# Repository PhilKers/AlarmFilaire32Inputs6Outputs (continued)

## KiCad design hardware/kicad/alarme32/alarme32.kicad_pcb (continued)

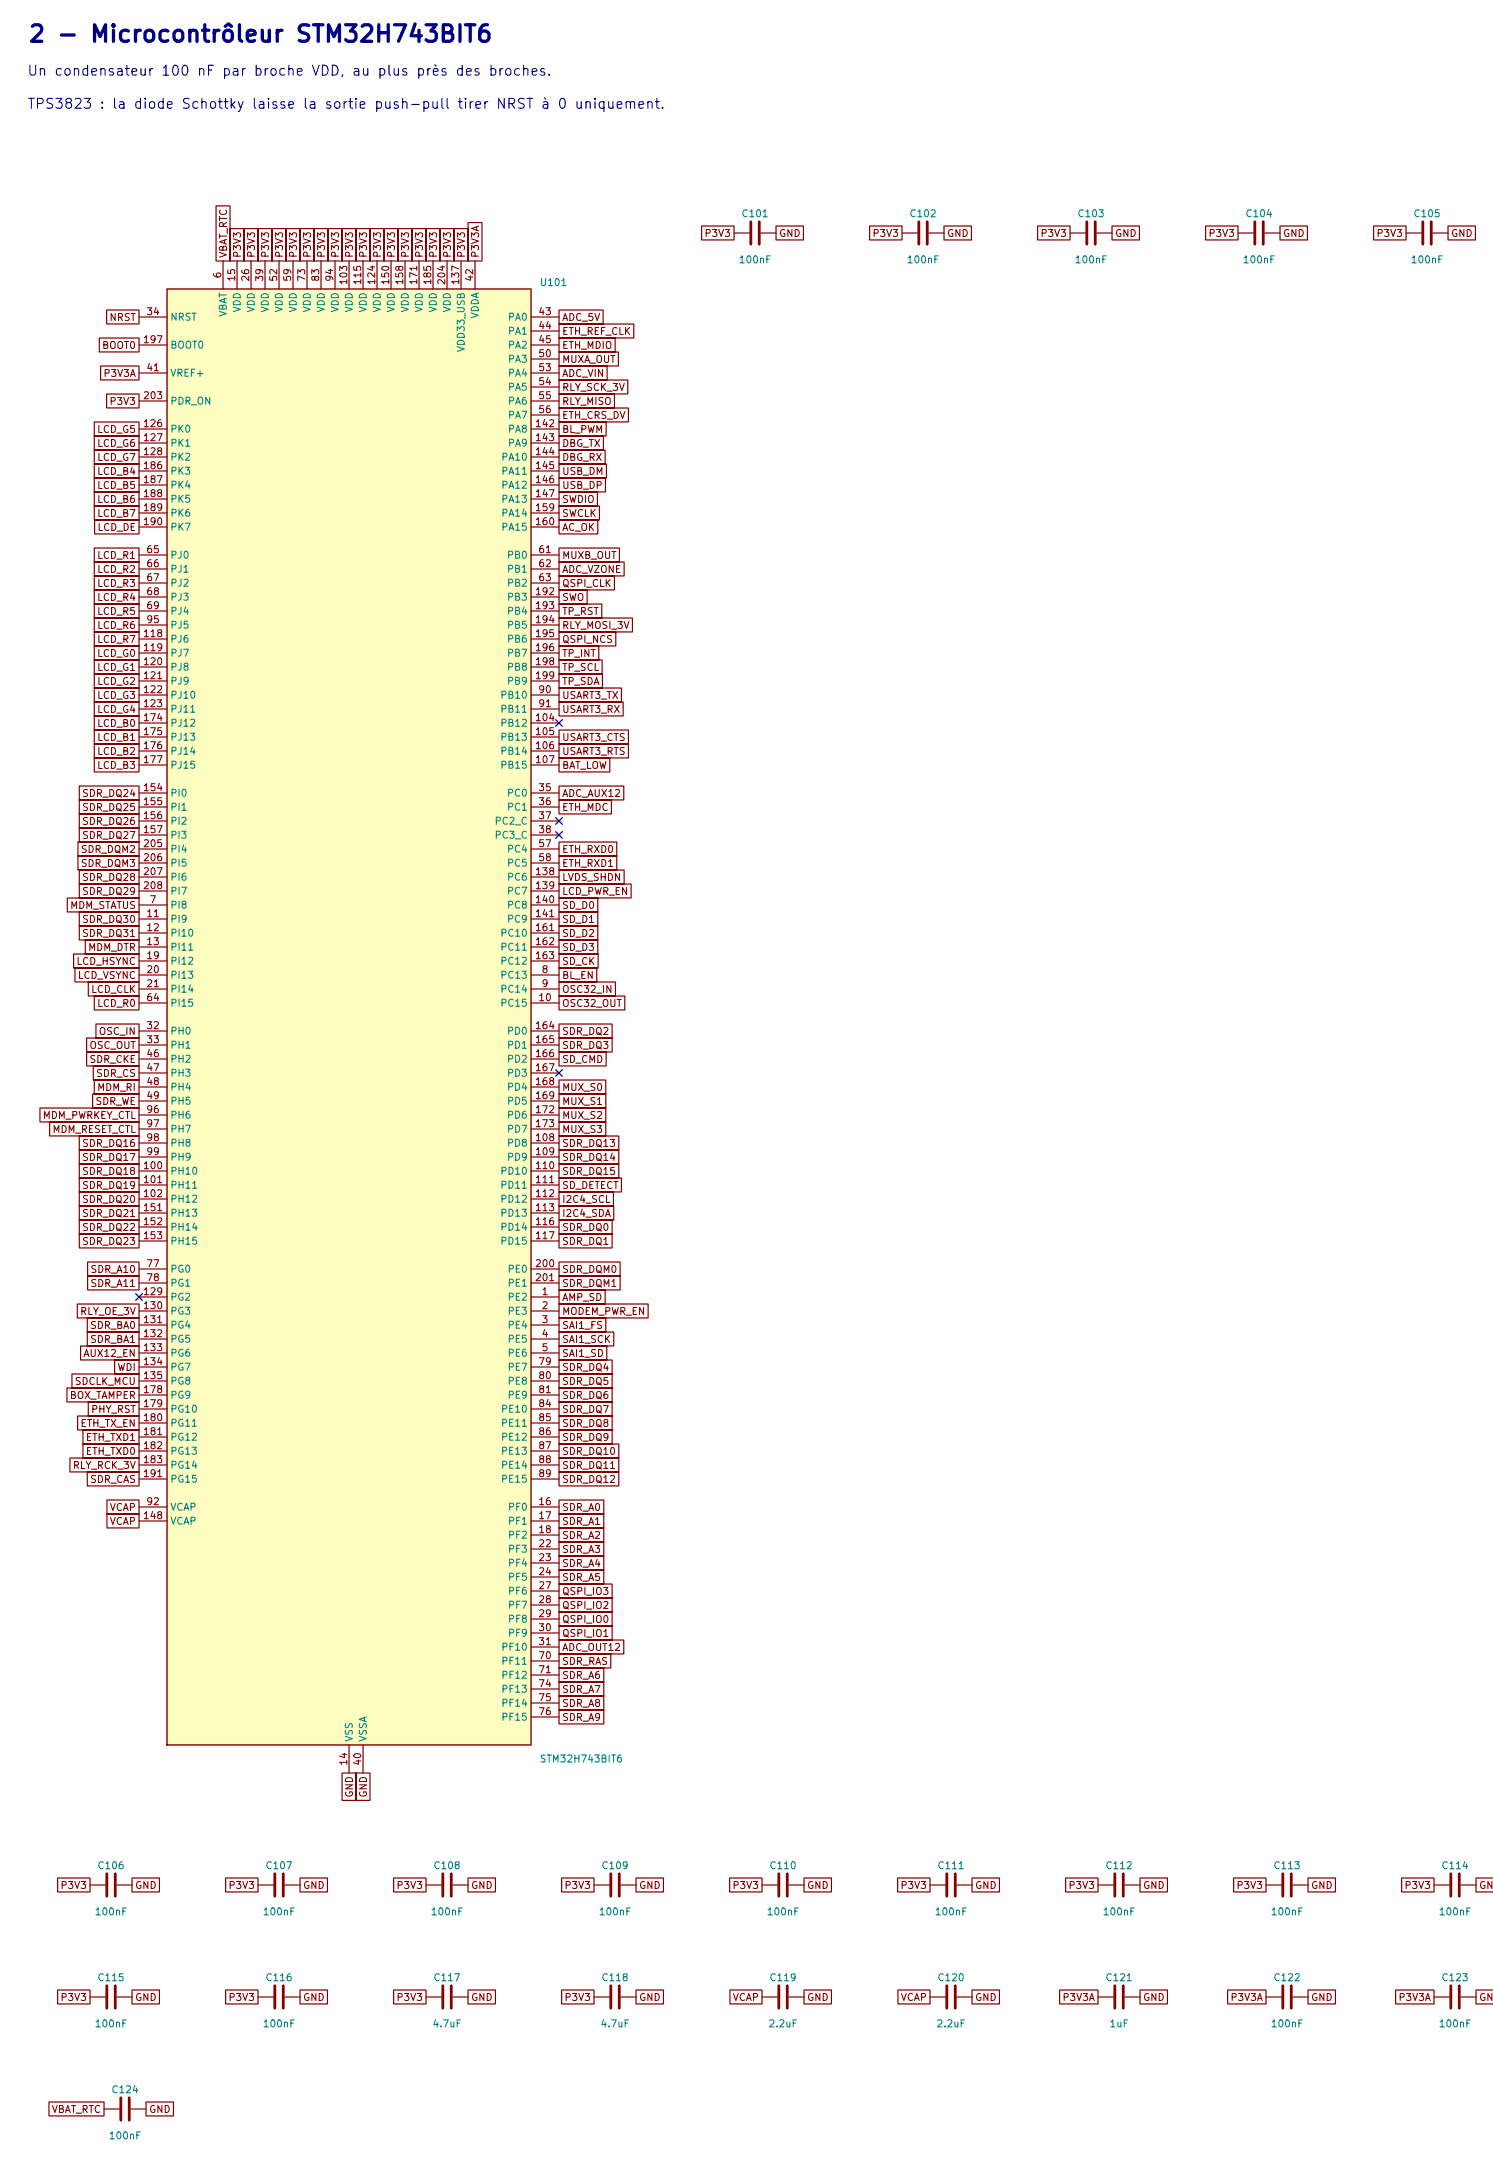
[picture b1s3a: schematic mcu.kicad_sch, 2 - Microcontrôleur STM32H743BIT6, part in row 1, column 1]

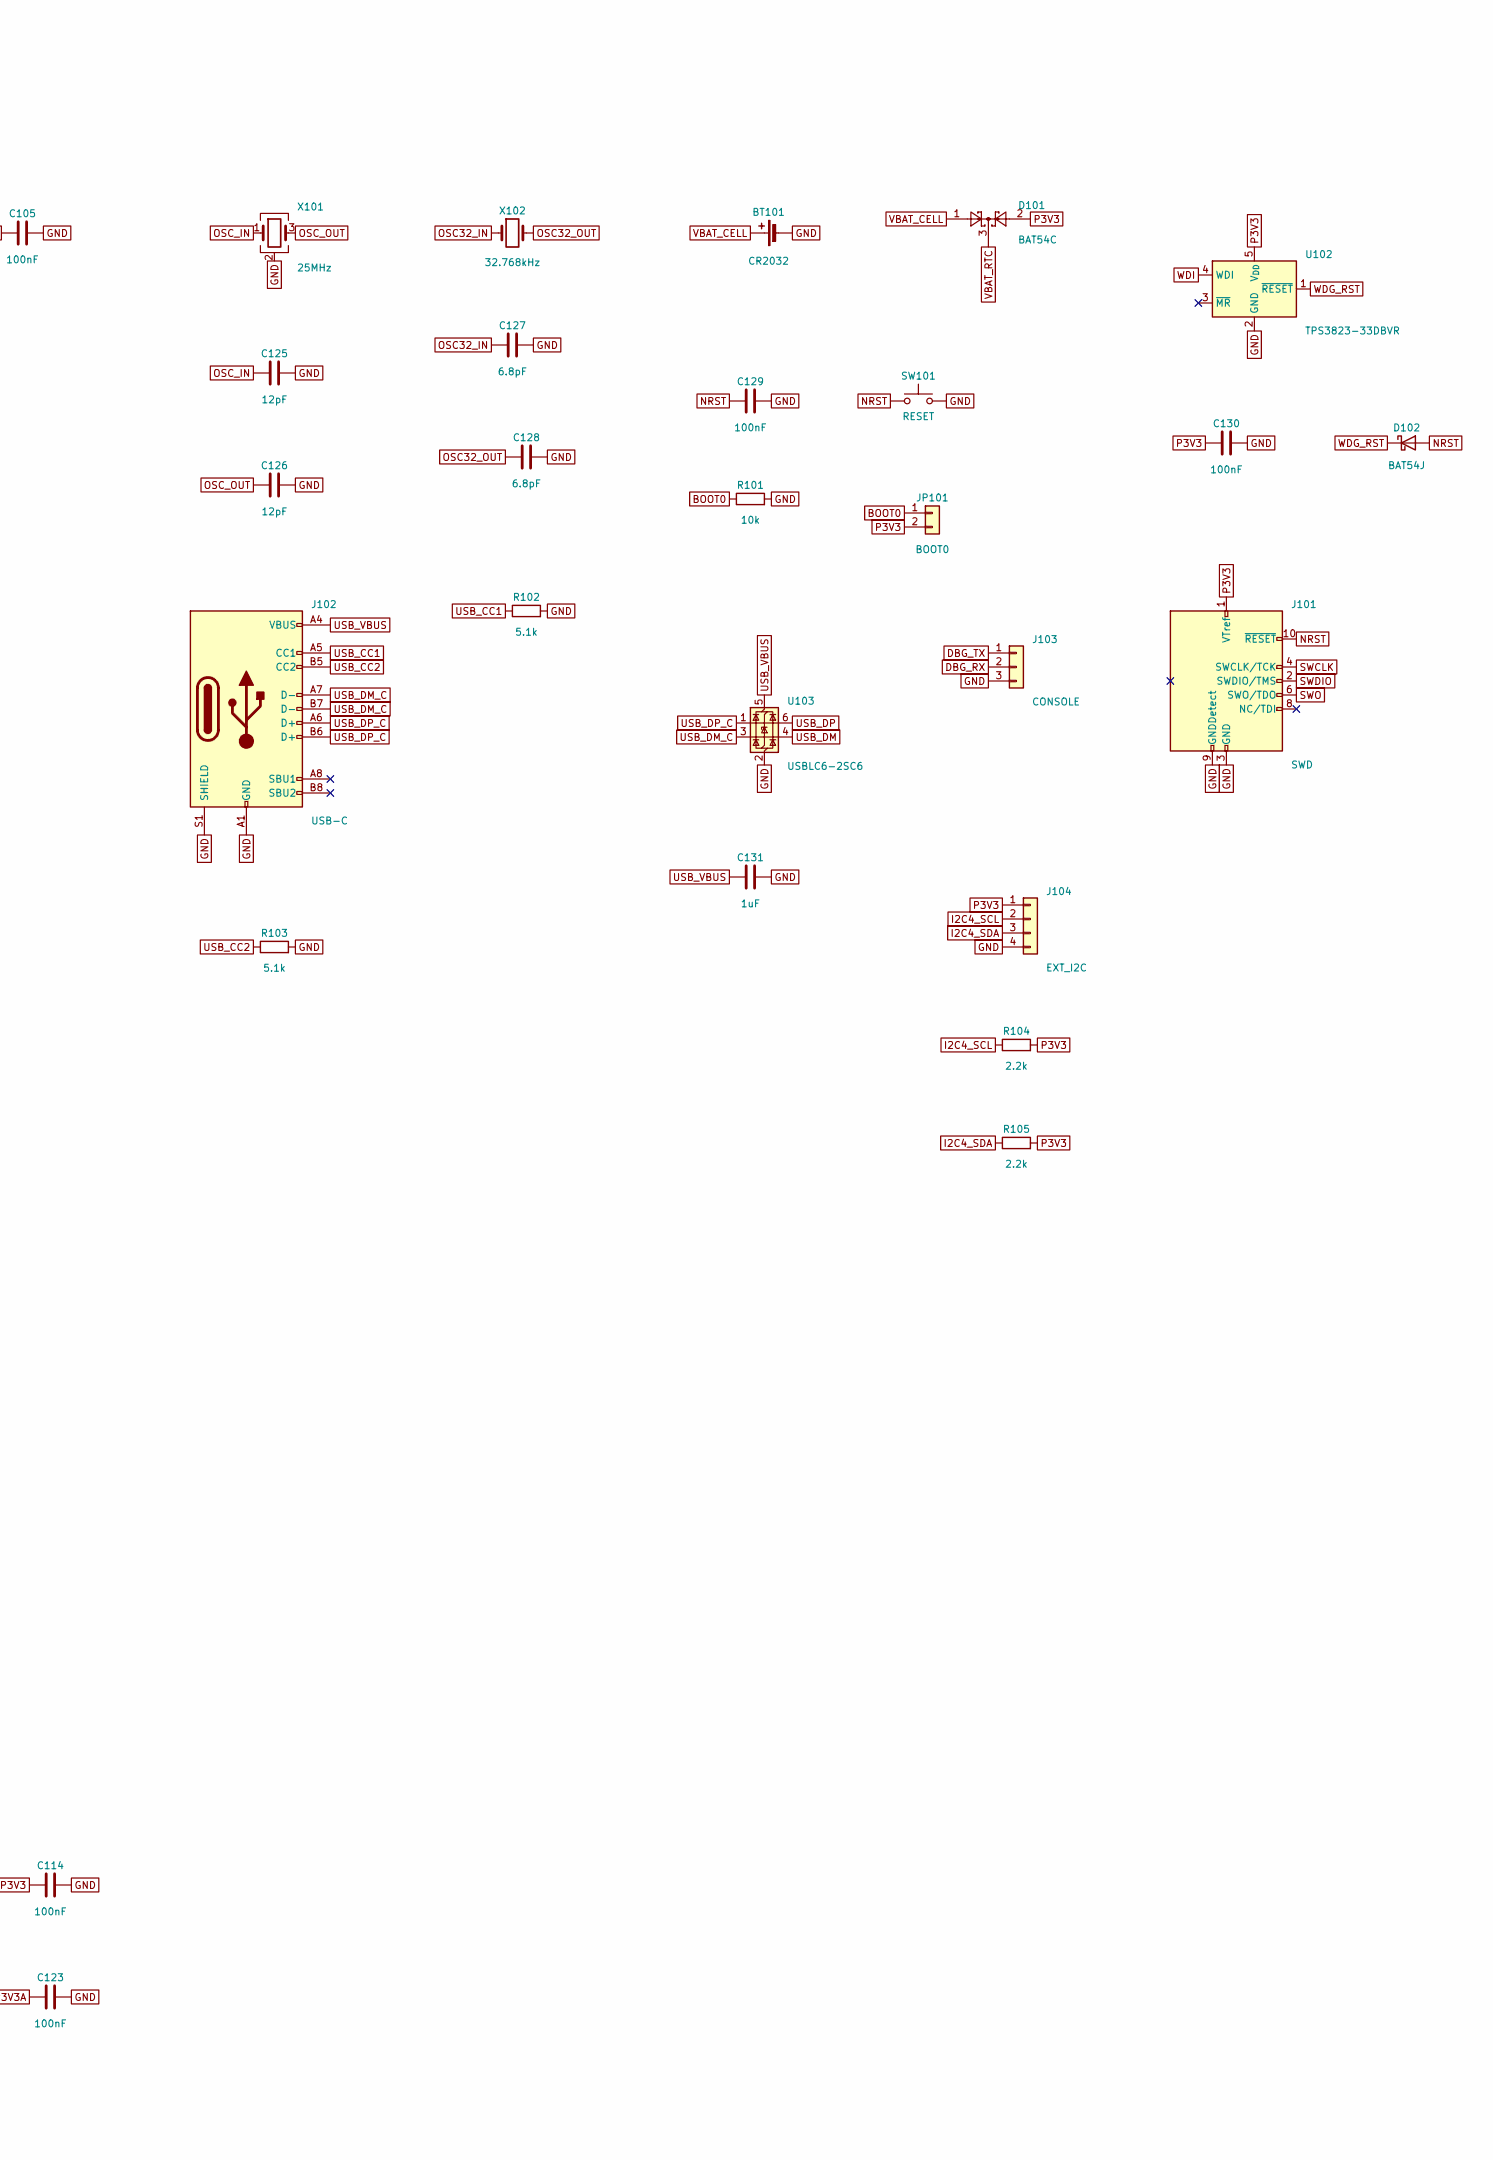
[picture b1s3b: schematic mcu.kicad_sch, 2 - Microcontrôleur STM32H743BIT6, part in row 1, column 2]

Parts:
BT101: CR2032; BatteryHolder_Keystone_3034_1x20mm
C101, C102, C103, C104, C105, C106, C107, C108, C109, C110, C111, C112, C113, C114, C115, C116, C122, C123, C124, C129, C130: 100nF; C_0603_1608Metric
C117, C118: 4.7uF; C_0805_2012Metric
C119, C120: 2.2uF; C_0603_1608Metric
C121, C131: 1uF; C_0603_1608Metric
C125, C126: 12pF; C_0603_1608Metric
C127, C128: 6.8pF; C_0603_1608Metric
D101: BAT54C; SOT-23
D102: BAT54J; D_SOD-323
J101: SWD; PinHeader_2x05_P1.27mm_Vertical
J102: USB-C; USB_C_Receptacle_HRO_TYPE-C-31-M-12
J103: CONSOLE; PinHeader_1x03_P2.54mm_Vertical
J104: EXT_I2C; PinHeader_1x04_P2.54mm_Vertical
JP101: BOOT0; PinHeader_1x02_P2.54mm_Vertical
R101: 10k; R_0603_1608Metric
R102, R103: 5.1k; R_0603_1608Metric
R104, R105: 2.2k; R_0603_1608Metric
SW101: RESET; SW_SPST_EVQP2
U101: STM32H743BIT6; LQFP-208_28x28mm_P0.5mm
U102: TPS3823-33DBVR; SOT-23-5
U103: USBLC6-2SC6; SOT-23-6
X101: 25MHz; Crystal_SMD_3225-4Pin_3.2x2.5mm
X102: 32.768kHz; Crystal_SMD_3215-2Pin_3.2x1.5mm

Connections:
AC_OK: U101.160 (PA15); also elsewhere on the board
ADC_5V: U101.43 (PA0); also elsewhere on the board
ADC_AUX12: U101.35 (PC0); also elsewhere on the board
ADC_OUT12: U101.31 (PF10); also elsewhere on the board
ADC_VIN: U101.53 (PA4); also elsewhere on the board
ADC_VZONE: U101.62 (PB1); also elsewhere on the board
AMP_SD: U101.1 (PE2); also elsewhere on the board
AUX12_EN: U101.133 (PG6); also elsewhere on the board
BAT_LOW: U101.107 (PB15); also elsewhere on the board
BL_EN: U101.8 (PC13); also elsewhere on the board
BL_PWM: U101.142 (PA8); also elsewhere on the board
BOOT0: JP101.1, R101.1, U101.197 (BOOT0)
BOX_TAMPER: U101.178 (PG9); also elsewhere on the board
DBG_RX: J103.2, U101.144 (PA10)
DBG_TX: J103.1, U101.143 (PA9)
ETH_CRS_DV: U101.56 (PA7); also elsewhere on the board
ETH_MDC: U101.36 (PC1); also elsewhere on the board
ETH_MDIO: U101.45 (PA2); also elsewhere on the board
ETH_REF_CLK: U101.44 (PA1); also elsewhere on the board
ETH_RXD0: U101.57 (PC4); also elsewhere on the board
ETH_RXD1: U101.58 (PC5); also elsewhere on the board
ETH_TXD0: U101.182 (PG13); also elsewhere on the board
ETH_TXD1: U101.181 (PG12); also elsewhere on the board
ETH_TX_EN: U101.180 (PG11); also elsewhere on the board
GND: BT101.2 (-), C101.2, C102.2, C103.2, C104.2, C105.2, C106.2, C107.2, C108.2, C109.2, C110.2, C111.2, C112.2, C113.2, C114.2, C115.2, C116.2, C117.2, C118.2, C119.2, C120.2, C121.2, C122.2, C123.2, C124.2, C125.2, C126.2, C127.2, C128.2, C129.2, C130.2, C131.2, J101.3 (GND), J101.5 (GND), J101.9 (GNDDetect), J102.A1 (GND), J102.A12 (GND), J102.B1 (GND), J102.B12 (GND), J102.S1 (SHIELD), J103.3, J104.4, R101.2, R102.2, R103.2, SW101.2, U101.14 (VSS), U101.25 (VSS), U101.40 (VSSA), U101.51 (VSS), U101.60 (VSS), U101.72 (VSS), U101.82 (VSS), U101.93 (VSS), U101.114 (VSS), U101.125 (VSS), U101.136 (VSS), U101.149 (VSS), U101.170 (VSS), U101.184 (VSS), U101.202 (VSS), U102.2 (GND), U103.2 (GND), X101.2 (G), X101.4 (G); also elsewhere on the board
I2C4_SCL: J104.2, R104.1, U101.112 (PD12); also elsewhere on the board
I2C4_SDA: J104.3, R105.1, U101.113 (PD13); also elsewhere on the board
LCD_B0: U101.174 (PJ12); also elsewhere on the board
LCD_B1: U101.175 (PJ13); also elsewhere on the board
LCD_B2: U101.176 (PJ14); also elsewhere on the board
LCD_B3: U101.177 (PJ15); also elsewhere on the board
LCD_B4: U101.186 (PK3); also elsewhere on the board
LCD_B5: U101.187 (PK4); also elsewhere on the board
LCD_B6: U101.188 (PK5); also elsewhere on the board
LCD_B7: U101.189 (PK6); also elsewhere on the board
LCD_CLK: U101.21 (PI14); also elsewhere on the board
LCD_DE: U101.190 (PK7); also elsewhere on the board
LCD_G0: U101.119 (PJ7); also elsewhere on the board
LCD_G1: U101.120 (PJ8); also elsewhere on the board
LCD_G2: U101.121 (PJ9); also elsewhere on the board
LCD_G3: U101.122 (PJ10); also elsewhere on the board
LCD_G4: U101.123 (PJ11); also elsewhere on the board
LCD_G5: U101.126 (PK0); also elsewhere on the board
LCD_G6: U101.127 (PK1); also elsewhere on the board
LCD_G7: U101.128 (PK2); also elsewhere on the board
LCD_HSYNC: U101.19 (PI12); also elsewhere on the board
LCD_PWR_EN: U101.139 (PC7); also elsewhere on the board
LCD_R0: U101.64 (PI15); also elsewhere on the board
LCD_R1: U101.65 (PJ0); also elsewhere on the board
LCD_R2: U101.66 (PJ1); also elsewhere on the board
LCD_R3: U101.67 (PJ2); also elsewhere on the board
LCD_R4: U101.68 (PJ3); also elsewhere on the board
LCD_R5: U101.69 (PJ4); also elsewhere on the board
LCD_R6: U101.95 (PJ5); also elsewhere on the board
LCD_R7: U101.118 (PJ6); also elsewhere on the board
LCD_VSYNC: U101.20 (PI13); also elsewhere on the board
LVDS_SHDN: U101.138 (PC6); also elsewhere on the board
MDM_DTR: U101.13 (PI11); also elsewhere on the board
MDM_PWRKEY_CTL: U101.96 (PH6); also elsewhere on the board
MDM_RESET_CTL: U101.97 (PH7); also elsewhere on the board
MDM_RI: U101.48 (PH4); also elsewhere on the board
MDM_STATUS: U101.7 (PI8); also elsewhere on the board
MODEM_PWR_EN: U101.2 (PE3); also elsewhere on the board
MUXA_OUT: U101.50 (PA3); also elsewhere on the board
MUXB_OUT: U101.61 (PB0); also elsewhere on the board
MUX_S0: U101.168 (PD4); also elsewhere on the board
MUX_S1: U101.169 (PD5); also elsewhere on the board
MUX_S2: U101.172 (PD6); also elsewhere on the board
MUX_S3: U101.173 (PD7); also elsewhere on the board
NRST: C129.1, D102.2 (A), J101.10 (~RESET), SW101.1, U101.34 (NRST)
OSC32_IN: C127.1, U101.9 (PC14), X102.1
OSC32_OUT: C128.1, U101.10 (PC15), X102.2
OSC_IN: C125.1, U101.32 (PH0), X101.1
OSC_OUT: C126.1, U101.33 (PH1), X101.3
P3V3: C101.1, C102.1, C103.1, C104.1, C105.1, C106.1, C107.1, C108.1, C109.1, C110.1, C111.1, C112.1, C113.1, C114.1, C115.1, C116.1, C117.1, C118.1, C130.1, D101.2, J101.1 (VTref), J104.1, JP101.2, R104.2, R105.2, U101.15 (VDD), U101.26 (VDD), U101.39 (VDD), U101.52 (VDD), U101.59 (VDD), U101.73 (VDD), U101.83 (VDD), U101.94 (VDD), U101.103 (VDD), U101.115 (VDD), U101.124 (VDD), U101.137 (VDD33_USB), U101.150 (VDD), U101.158 (VDD), U101.171 (VDD), U101.185 (VDD), U101.203 (PDR_ON), U101.204 (VDD), U102.5 (V_{DD}); also elsewhere on the board
P3V3A: C121.1, C122.1, C123.1, U101.41 (VREF+), U101.42 (VDDA); also elsewhere on the board
PHY_RST: U101.179 (PG10); also elsewhere on the board
QSPI_CLK: U101.63 (PB2); also elsewhere on the board
QSPI_IO0: U101.29 (PF8); also elsewhere on the board
QSPI_IO1: U101.30 (PF9); also elsewhere on the board
QSPI_IO2: U101.28 (PF7); also elsewhere on the board
QSPI_IO3: U101.27 (PF6); also elsewhere on the board
QSPI_NCS: U101.195 (PB6); also elsewhere on the board
RLY_MISO: U101.55 (PA6); also elsewhere on the board
RLY_MOSI_3V: U101.194 (PB5); also elsewhere on the board
RLY_OE_3V: U101.130 (PG3); also elsewhere on the board
RLY_RCK_3V: U101.183 (PG14); also elsewhere on the board
RLY_SCK_3V: U101.54 (PA5); also elsewhere on the board
SAI1_FS: U101.3 (PE4); also elsewhere on the board
SAI1_SCK: U101.4 (PE5); also elsewhere on the board
SAI1_SD: U101.5 (PE6); also elsewhere on the board
SDCLK_MCU: U101.135 (PG8); also elsewhere on the board
SDR_A0: U101.16 (PF0); also elsewhere on the board
SDR_A1: U101.17 (PF1); also elsewhere on the board
SDR_A2: U101.18 (PF2); also elsewhere on the board
SDR_A3: U101.22 (PF3); also elsewhere on the board
SDR_A4: U101.23 (PF4); also elsewhere on the board
SDR_A5: U101.24 (PF5); also elsewhere on the board
SDR_A6: U101.71 (PF12); also elsewhere on the board
SDR_A7: U101.74 (PF13); also elsewhere on the board
SDR_A8: U101.75 (PF14); also elsewhere on the board
SDR_A9: U101.76 (PF15); also elsewhere on the board
SDR_A10: U101.77 (PG0); also elsewhere on the board
SDR_A11: U101.78 (PG1); also elsewhere on the board
SDR_BA0: U101.131 (PG4); also elsewhere on the board
SDR_BA1: U101.132 (PG5); also elsewhere on the board
SDR_CAS: U101.191 (PG15); also elsewhere on the board
SDR_CKE: U101.46 (PH2); also elsewhere on the board
SDR_CS: U101.47 (PH3); also elsewhere on the board
SDR_DQ0: U101.116 (PD14); also elsewhere on the board
SDR_DQ1: U101.117 (PD15); also elsewhere on the board
SDR_DQ2: U101.164 (PD0); also elsewhere on the board
SDR_DQ3: U101.165 (PD1); also elsewhere on the board
SDR_DQ4: U101.79 (PE7); also elsewhere on the board
SDR_DQ5: U101.80 (PE8); also elsewhere on the board
SDR_DQ6: U101.81 (PE9); also elsewhere on the board
SDR_DQ7: U101.84 (PE10); also elsewhere on the board
SDR_DQ8: U101.85 (PE11); also elsewhere on the board
SDR_DQ9: U101.86 (PE12); also elsewhere on the board
SDR_DQ10: U101.87 (PE13); also elsewhere on the board
SDR_DQ11: U101.88 (PE14); also elsewhere on the board
SDR_DQ12: U101.89 (PE15); also elsewhere on the board
SDR_DQ13: U101.108 (PD8); also elsewhere on the board
SDR_DQ14: U101.109 (PD9); also elsewhere on the board
SDR_DQ15: U101.110 (PD10); also elsewhere on the board
SDR_DQ16: U101.98 (PH8); also elsewhere on the board
SDR_DQ17: U101.99 (PH9); also elsewhere on the board
SDR_DQ18: U101.100 (PH10); also elsewhere on the board
SDR_DQ19: U101.101 (PH11); also elsewhere on the board
SDR_DQ20: U101.102 (PH12); also elsewhere on the board
SDR_DQ21: U101.151 (PH13); also elsewhere on the board
SDR_DQ22: U101.152 (PH14); also elsewhere on the board
SDR_DQ23: U101.153 (PH15); also elsewhere on the board
SDR_DQ24: U101.154 (PI0); also elsewhere on the board
SDR_DQ25: U101.155 (PI1); also elsewhere on the board
SDR_DQ26: U101.156 (PI2); also elsewhere on the board
SDR_DQ27: U101.157 (PI3); also elsewhere on the board
SDR_DQ28: U101.207 (PI6); also elsewhere on the board
SDR_DQ29: U101.208 (PI7); also elsewhere on the board
SDR_DQ30: U101.11 (PI9); also elsewhere on the board
SDR_DQ31: U101.12 (PI10); also elsewhere on the board
SDR_DQM0: U101.200 (PE0); also elsewhere on the board
SDR_DQM1: U101.201 (PE1); also elsewhere on the board
SDR_DQM2: U101.205 (PI4); also elsewhere on the board
SDR_DQM3: U101.206 (PI5); also elsewhere on the board
SDR_RAS: U101.70 (PF11); also elsewhere on the board
SDR_WE: U101.49 (PH5); also elsewhere on the board
SD_CK: U101.163 (PC12); also elsewhere on the board
SD_CMD: U101.166 (PD2); also elsewhere on the board
SD_D0: U101.140 (PC8); also elsewhere on the board
SD_D1: U101.141 (PC9); also elsewhere on the board
SD_D2: U101.161 (PC10); also elsewhere on the board
SD_D3: U101.162 (PC11); also elsewhere on the board
SD_DETECT: U101.111 (PD11); also elsewhere on the board
SWCLK: J101.4 (SWCLK/TCK), U101.159 (PA14)
SWDIO: J101.2 (SWDIO/TMS), U101.147 (PA13)
SWO: J101.6 (SWO/TDO), U101.192 (PB3)
TP_INT: U101.196 (PB7); also elsewhere on the board
TP_RST: U101.193 (PB4); also elsewhere on the board
TP_SCL: U101.198 (PB8); also elsewhere on the board
TP_SDA: U101.199 (PB9); also elsewhere on the board
USART3_CTS: U101.105 (PB13); also elsewhere on the board
USART3_RTS: U101.106 (PB14); also elsewhere on the board
USART3_RX: U101.91 (PB11); also elsewhere on the board
USART3_TX: U101.90 (PB10); also elsewhere on the board
USB_CC1: J102.A5 (CC1), R102.1
USB_CC2: J102.B5 (CC2), R103.1
USB_DM: U101.145 (PA11), U103.4 (I/O2)
USB_DM_C: J102.A7 (D-), J102.B7 (D-), U103.3 (I/O2)
USB_DP: U101.146 (PA12), U103.6 (I/O1)
USB_DP_C: J102.A6 (D+), J102.B6 (D+), U103.1 (I/O1)
USB_VBUS: C131.1, J102.A4 (VBUS), J102.A9 (VBUS), J102.B4 (VBUS), J102.B9 (VBUS), U103.5 (VBUS)
VBAT_CELL: BT101.1 (+), D101.1
VBAT_RTC: C124.1, D101.3, U101.6 (VBAT)
VCAP: C119.1, C120.1, U101.92 (VCAP), U101.148 (VCAP)
WDG_RST: D102.1 (K), U102.1 (~RESET)
WDI: U101.134 (PG7), U102.4 (WDI)

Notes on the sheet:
2 - Microcontrôleur STM32H743BIT6
Un condensateur 100 nF par broche VDD, au plus près des broches.
TPS3823 : la diode Schottky laisse la sortie push-pull tirer NRST à 0 uniquement.

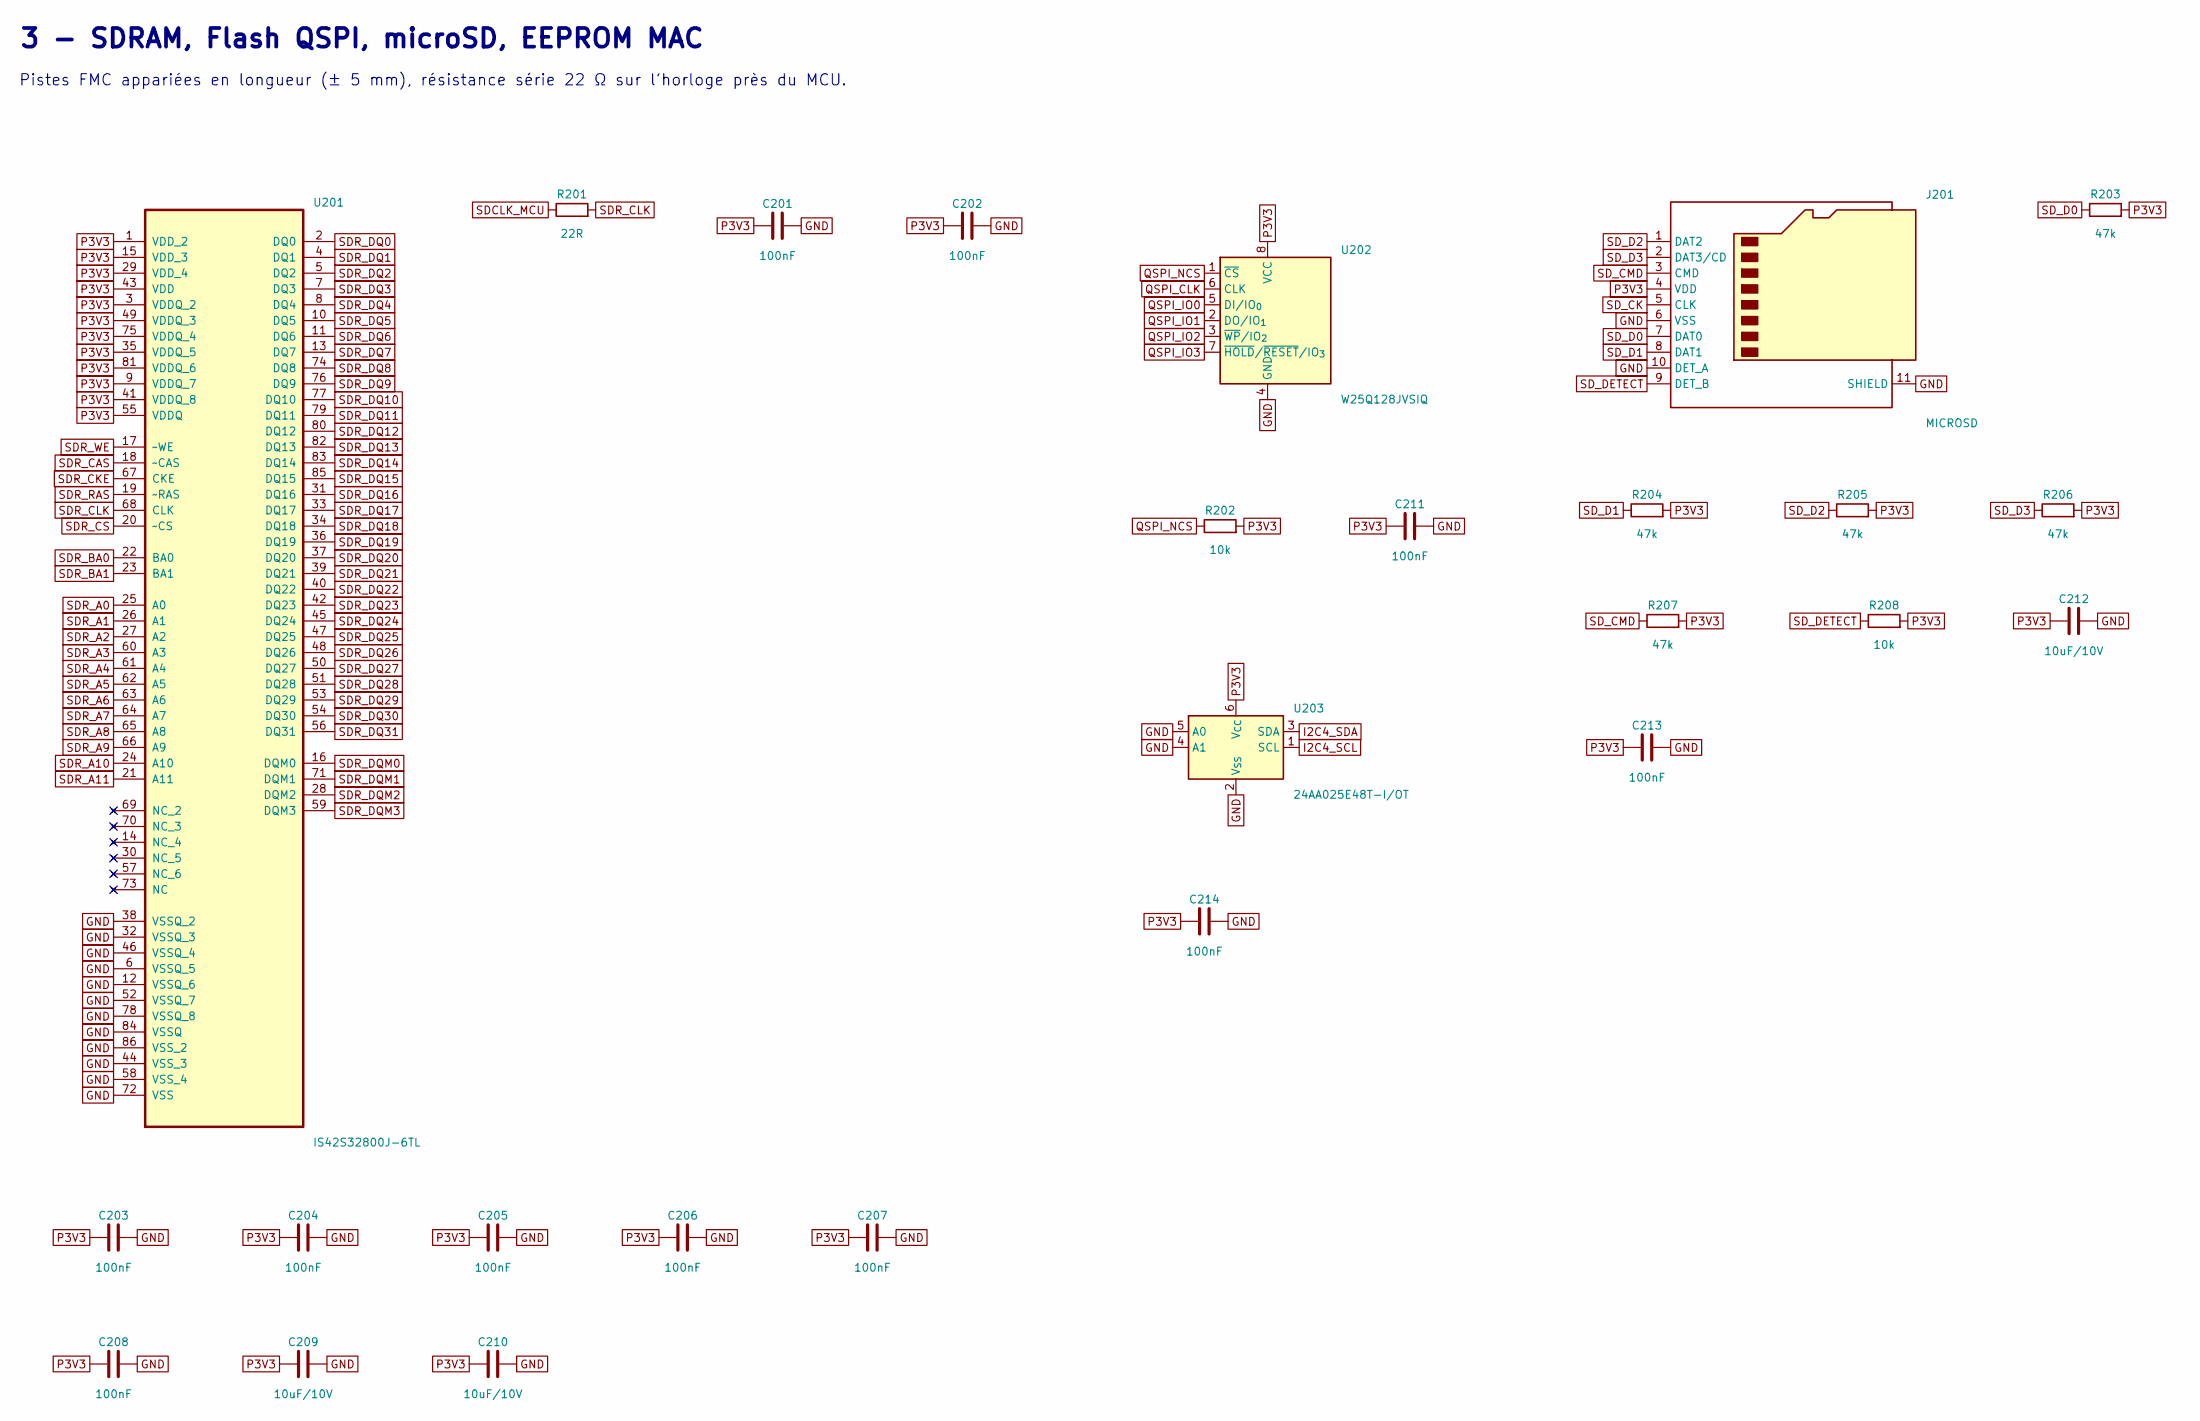
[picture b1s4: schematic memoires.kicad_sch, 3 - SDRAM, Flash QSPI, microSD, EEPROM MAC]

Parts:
C201, C202, C203, C204, C205, C206, C207, C208, C211, C213, C214: 100nF; C_0603_1608Metric
C209, C210, C212: 10uF/10V; C_0805_2012Metric
J201: MICROSD; microSD_HC_Hirose_DM3AT-SF-PEJM5
R201: 22R; R_0603_1608Metric
R202, R208: 10k; R_0603_1608Metric
R203, R204, R205, R206, R207: 47k; R_0603_1608Metric
U201: IS42S32800J-6TL; TSOP-II-86_22.22x10.16mm_P0.5mm
U202: W25Q128JVSIQ; SOIC-8_5.23x5.23mm_P1.27mm
U203: 24AA025E48T-I/OT; SOT-23-6

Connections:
GND: C201.2, C202.2, C203.2, C204.2, C205.2, C206.2, C207.2, C208.2, C209.2, C210.2, C211.2, C212.2, C213.2, C214.2, J201.6 (VSS), J201.10 (DET_A), J201.11 (SHIELD), U201.6 (VSSQ_5), U201.12 (VSSQ_6), U201.32 (VSSQ_3), U201.38 (VSSQ_2), U201.44 (VSS_3), U201.46 (VSSQ_4), U201.52 (VSSQ_7), U201.58 (VSS_4), U201.72 (VSS), U201.78 (VSSQ_8), U201.84 (VSSQ), U201.86 (VSS_2), U202.4 (GND), U203.2 (V_{SS}), U203.4 (A1), U203.5 (A0); also elsewhere on the board
I2C4_SCL: U203.1 (SCL); also elsewhere on the board
I2C4_SDA: U203.3 (SDA); also elsewhere on the board
P3V3: C201.1, C202.1, C203.1, C204.1, C205.1, C206.1, C207.1, C208.1, C209.1, C210.1, C211.1, C212.1, C213.1, C214.1, J201.4 (VDD), R202.2, R203.2, R204.2, R205.2, R206.2, R207.2, R208.2, U201.1 (VDD_2), U201.3 (VDDQ_2), U201.9 (VDDQ_7), U201.15 (VDD_3), U201.29 (VDD_4), U201.35 (VDDQ_5), U201.41 (VDDQ_8), U201.43 (VDD), U201.49 (VDDQ_3), U201.55 (VDDQ), U201.75 (VDDQ_4), U201.81 (VDDQ_6), U202.8 (VCC), U203.6 (V_{CC}); also elsewhere on the board
QSPI_CLK: U202.6 (CLK); also elsewhere on the board
QSPI_IO0: U202.5 (DI/IO_{0}); also elsewhere on the board
QSPI_IO1: U202.2 (DO/IO_{1}); also elsewhere on the board
QSPI_IO2: U202.3 (~WP/IO_{2}); also elsewhere on the board
QSPI_IO3: U202.7 (~HOLD/~RESET/IO_{3}); also elsewhere on the board
QSPI_NCS: R202.1, U202.1 (~CS); also elsewhere on the board
SDCLK_MCU: R201.1; also elsewhere on the board
SDR_A0: U201.25 (A0); also elsewhere on the board
SDR_A1: U201.26 (A1); also elsewhere on the board
SDR_A2: U201.27 (A2); also elsewhere on the board
SDR_A3: U201.60 (A3); also elsewhere on the board
SDR_A4: U201.61 (A4); also elsewhere on the board
SDR_A5: U201.62 (A5); also elsewhere on the board
SDR_A6: U201.63 (A6); also elsewhere on the board
SDR_A7: U201.64 (A7); also elsewhere on the board
SDR_A8: U201.65 (A8); also elsewhere on the board
SDR_A9: U201.66 (A9); also elsewhere on the board
SDR_A10: U201.24 (A10); also elsewhere on the board
SDR_A11: U201.21 (A11); also elsewhere on the board
SDR_BA0: U201.22 (BA0); also elsewhere on the board
SDR_BA1: U201.23 (BA1); also elsewhere on the board
SDR_CAS: U201.18 (~CAS); also elsewhere on the board
SDR_CKE: U201.67 (CKE); also elsewhere on the board
SDR_CLK: R201.2, U201.68 (CLK)
SDR_CS: U201.20 (~CS); also elsewhere on the board
SDR_DQ0: U201.2 (DQ0); also elsewhere on the board
SDR_DQ1: U201.4 (DQ1); also elsewhere on the board
SDR_DQ2: U201.5 (DQ2); also elsewhere on the board
SDR_DQ3: U201.7 (DQ3); also elsewhere on the board
SDR_DQ4: U201.8 (DQ4); also elsewhere on the board
SDR_DQ5: U201.10 (DQ5); also elsewhere on the board
SDR_DQ6: U201.11 (DQ6); also elsewhere on the board
SDR_DQ7: U201.13 (DQ7); also elsewhere on the board
SDR_DQ8: U201.74 (DQ8); also elsewhere on the board
SDR_DQ9: U201.76 (DQ9); also elsewhere on the board
SDR_DQ10: U201.77 (DQ10); also elsewhere on the board
SDR_DQ11: U201.79 (DQ11); also elsewhere on the board
SDR_DQ12: U201.80 (DQ12); also elsewhere on the board
SDR_DQ13: U201.82 (DQ13); also elsewhere on the board
SDR_DQ14: U201.83 (DQ14); also elsewhere on the board
SDR_DQ15: U201.85 (DQ15); also elsewhere on the board
SDR_DQ16: U201.31 (DQ16); also elsewhere on the board
SDR_DQ17: U201.33 (DQ17); also elsewhere on the board
SDR_DQ18: U201.34 (DQ18); also elsewhere on the board
SDR_DQ19: U201.36 (DQ19); also elsewhere on the board
SDR_DQ20: U201.37 (DQ20); also elsewhere on the board
SDR_DQ21: U201.39 (DQ21); also elsewhere on the board
SDR_DQ22: U201.40 (DQ22); also elsewhere on the board
SDR_DQ23: U201.42 (DQ23); also elsewhere on the board
SDR_DQ24: U201.45 (DQ24); also elsewhere on the board
SDR_DQ25: U201.47 (DQ25); also elsewhere on the board
SDR_DQ26: U201.48 (DQ26); also elsewhere on the board
SDR_DQ27: U201.50 (DQ27); also elsewhere on the board
SDR_DQ28: U201.51 (DQ28); also elsewhere on the board
SDR_DQ29: U201.53 (DQ29); also elsewhere on the board
SDR_DQ30: U201.54 (DQ30); also elsewhere on the board
SDR_DQ31: U201.56 (DQ31); also elsewhere on the board
SDR_DQM0: U201.16 (DQM0); also elsewhere on the board
SDR_DQM1: U201.71 (DQM1); also elsewhere on the board
SDR_DQM2: U201.28 (DQM2); also elsewhere on the board
SDR_DQM3: U201.59 (DQM3); also elsewhere on the board
SDR_RAS: U201.19 (~RAS); also elsewhere on the board
SDR_WE: U201.17 (~WE); also elsewhere on the board
SD_CK: J201.5 (CLK); also elsewhere on the board
SD_CMD: J201.3 (CMD), R207.1; also elsewhere on the board
SD_D0: J201.7 (DAT0), R203.1; also elsewhere on the board
SD_D1: J201.8 (DAT1), R204.1; also elsewhere on the board
SD_D2: J201.1 (DAT2), R205.1; also elsewhere on the board
SD_D3: J201.2 (DAT3/CD), R206.1; also elsewhere on the board
SD_DETECT: J201.9 (DET_B), R208.1; also elsewhere on the board

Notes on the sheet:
3 - SDRAM, Flash QSPI, microSD, EEPROM MAC
Pistes FMC appariées en longueur (± 5 mm), résistance série 22 Ω sur l'horloge près du MCU.
